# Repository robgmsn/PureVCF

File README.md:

View this project on [CADLAB.io](https://cadlab.io/project/24191). 

# PureVCF

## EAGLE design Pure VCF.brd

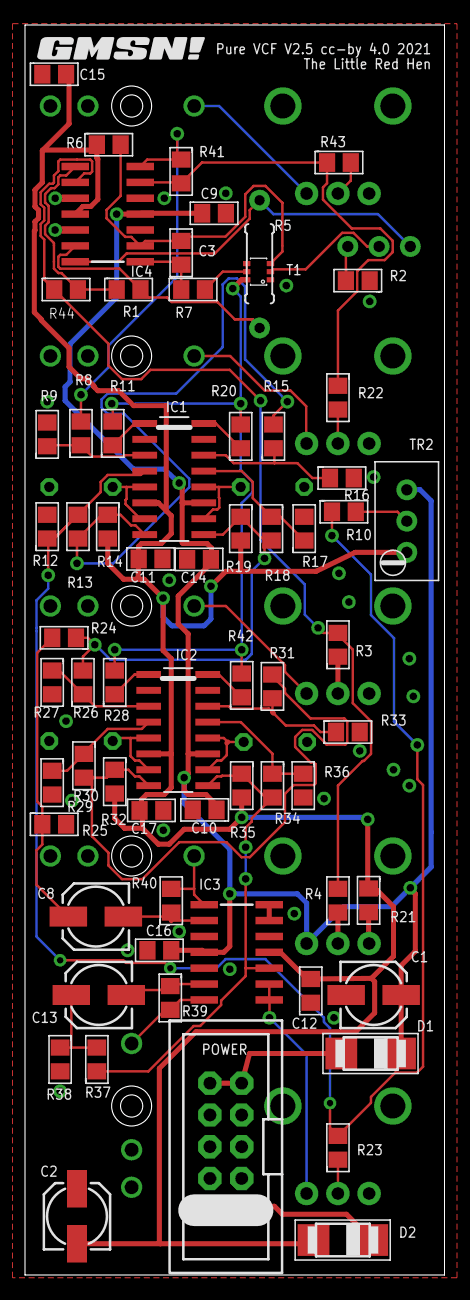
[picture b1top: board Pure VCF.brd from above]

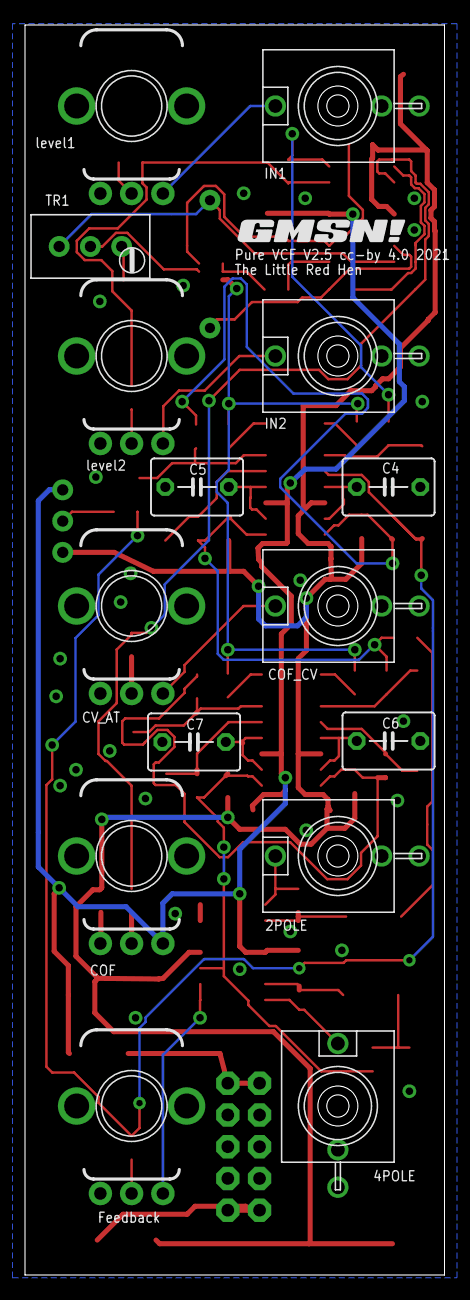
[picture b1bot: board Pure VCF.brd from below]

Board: 2 copper layers, 33.6 x 100.0 mm, 83 parts (16 on the bottom side), 55 nets.

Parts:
2POLE, 4POLE: PJ301M-12
C1, C2, C8, C13: 10uF; 153CLV-0505
C3: 22pF; C0805
C4, C5, C6, C7: 220p; C050-045X075
C9, C10, C11, C12, C14, C15, C16, C17: 100nF; C0805
COF: 10k; POT_9MM_RED_KNOB
COF_CV: PJ301M-12
CV_AT: 10k; POT_9MM_GREEN_KNOB
D1, D2: STTH102A; SMADIODE
IC1, IC2: LM13700; SOIC-16_BLANK
IC3, IC4: TL074; SO14
IN1, IN2: PJ301M-12
IN1POT, IN1POT1: 10k; POT_9MM_BLUE_KNOB
JP1: HEADER2X5SHD; 2X5-SHROUDED
Q: 10k; POT_9MM_YELLOW_KNOB
R1, R3, R4, R14, R19, R22, R23, R24, R25, R32, R35, R37, R38, R39, R40, R41, R43, R44: 10k; R0805
R2: 390R; R0805
R5: Tempco 2k; 0207/8.5
R6: 2M; R0805
R7: 2k2; R0805
R8, R10, R13, R15, R18, R26, R30, R31, R34: 100k; R0805
R9, R12, R16, R17, R27, R29, R33, R36: 220R; R0805
R11, R20, R28, R42: 33k; R0805
R21: 75k; R0805
T1: DMMT3906W; TRANS_PAIR
TR1, TR2: 100k; TRIMMER_TH
U$1, U$2: GMSN!_LOGO

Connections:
+12V: C1.+, C9.1, C10.1, C14.1, C16.1, COF.P$3, D1.C, IC1.11, IC2.11, IC3.4, IC4.4, TR2.3
-12V: C2.-, C11.2, C12.2, C15.2, C17.2, D2.A, IC1.6, IC2.6, IC3.11, IC4.11, R6.1, R14.2, R19.2, R21.1, R32.2, R35.2, TR2.1
GND: 2POLE.GND, 4POLE.GND, C1.-, C2.+, C4.2, C5.2, C6.2, C7.2, C9.2, C10.2, C11.1, C12.1, C14.2, C15.1, C16.2, C17.1, COF_CV.GND, COF_CV.NORM, CV_AT.P$1, IC3.3, IC3.5, IC3.12, IC4.3, IC4.5, IC4.10, IC4.12, IN1.GND, IN1POT.P$1, IN1POT1.P$1, IN2.GND, JP1.3, JP1.4, JP1.5, JP1.6, JP1.7, JP1.8, Q.P$1, R2.1, R9.2, R12.2, R16.2, R17.2, R25.2, R27.2, R29.2, R33.2, R36.2, R38.2, T1.1
unnamed: C5.1, IC1.10, IC1.12
unnamed: T1.2, TR1.2
unnamed: R2.2, TR1.1
unnamed: IC1.4, R10.1, R12.1, R13.1, R23.2
unnamed: IC4.14, R5.2, TR1.3
unnamed: IC4.13, R1.2, R5.1
unnamed: COF_CV.TIP, CV_AT.P$3
unnamed: CV_AT.P$2, R3.1
unnamed: COF.P$2, R4.1
unnamed: C3.1, IC4.2, R6.2, T1.3
unnamed: C3.2, IC4.1, R7.1
unnamed: IC1.1, R11.1
unnamed: R7.2, T1.4, T1.5
unnamed: IC4.6, R22.1, R41.2, R43.1
unnamed: IC1.9, R18.2, R19.1, R24.1, R26.2
unnamed: IC1.3, R8.1, R9.1
unnamed: C8.-, IC3.2, R40.1
unnamed: Q.P$2, R23.1
unnamed: IC3.8, IC3.9, Q.P$3
unnamed: C13.-, IC3.6, R39.1
unnamed: IC1.16, R20.1
unnamed: IC1.14, R15.1, R16.1
unnamed: IC1.13, R17.1, R18.1
unnamed: COF.P$1, R21.2
unnamed: C8.+, R24.2, R25.1
unnamed: C4.1, IC1.5, IC1.7
unnamed: IC1.8, R13.2, R14.1, R15.2
unnamed: IC2.3, R26.1, R27.1
unnamed: 2POLE.TIP, IC3.1, R40.2
unnamed: IC2.16, R42.1
unnamed: IC4.7, R8.2, R41.1
unnamed: IC2.4, R29.1, R30.1
unnamed: IC4.8, R1.1, R44.2
unnamed: R11.2, R20.2, R28.2, R42.2, T1.6
unnamed: C13.+, R37.2, R38.1
unnamed: IC3.13, IC3.14
unnamed: D1.A, JP1.9, JP1.10
unnamed: IC4.9, R3.2, R4.2, R44.1
unnamed: IC2.13, R34.1, R36.1
unnamed: 4POLE.TIP, IC3.7, R39.2
unnamed: IC2.14, R31.1, R33.1
unnamed: IC2.8, R30.2, R31.2, R32.1
unnamed: IC2.9, IC3.10, R34.2, R35.1, R37.1
unnamed: IN1.TIP, IN1POT.P$3
unnamed: IN1POT1.P$3, IN2.TIP
unnamed: D2.C, JP1.1, JP1.2
unnamed: IN1POT.P$2, R43.2
unnamed: R10.2, TR2.2
unnamed: IN1POT1.P$2, R22.2
unnamed: C6.1, IC2.5, IC2.7
unnamed: C7.1, IC2.10, IC2.12
unnamed: IC2.1, R28.1

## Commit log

2021-04-16 VCF 2.1
    Converted to SMD and switched from RS Design Spark to Eagle.
2021-04-16 VCF 2.2
2021-04-16 Backlink to CADLAB.io has been added.
2021-04-16 VCF 2.3
2021-04-16 VCF 2.4
2021-04-16 VCF 2.5 beta
    VCF Updated to V2.5 14/04/21
    Library updated to 3D models.
    Changed the CV mixer from Average to Sum and added inverter stage to retain consistency.
    Some resistor values reduced to 10K, inline with low noise techniques.
    Rerouted and reduced some traces.
2021-07-07 Reinstall

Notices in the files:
Pure VCF.brd:
Pure VCF V2.5 cc-by 4.0 2021
